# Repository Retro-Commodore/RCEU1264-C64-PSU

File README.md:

# C64-PSU
A C64/C128/Vic20/Plus4 PSU
This is a full replacement PSU with modern electronics that won't kill your computer when it gets bad.. the original PSU's short input to output, when they break, feeding approx 10v.
While it is possible to use wall warts, this design is created to be easy to diy, somewhat pretty and closer to the old designs with off the shelf items.

Greetz to Trap/Bonzai for being the source of inspiration to create this.

The PSU can be used for the C64 even with i.e. 1541 Ultimate and Vic20, and it's powerful enough to feed the C128 and/or 17xx REU.

All parts can be bought at [tme.eu](https://www.tme.eu/), and the pcb has been designed with parts from there.
A few parts like the DIN connector and fuse socket can be aqcuired from ebay where they're much cheaper.

*If you are a reseller, and use my designs, though the projects are open source, I'd like to ask you to donate a small amount of money, to cancer research for each sold device.*

The Mean Well IRM-20-5 is Short circuit / Overload / Over voltage protected (pdf's from Mean Well are in the documentation folder).

**The trafo is a 230v trafo, so countries that use 115v will need a different trafo.**

If you want to add an on/off switch, the easiest might be a switch on the 230v cable, or a round one, the round one is easiest to make holes to -by drilling-, rather than cutting a square one. But that is entirely up to you :-) .

The gerber files which is the zip file found in [hardware/eagle](https://github.com/Retro-Commodore/C64-PSU/tree/master/Hardware/Eagle Gerber) can be uploaded as is to PCB manufacturing companies like [JLCPCB](http://jlcpcb.com).

The PCB is created with Eagle which has a limiting size of 100x100mm (or is it 100x80mm?). And the PCB is within this size.
The newest version of KiCAD should be able to import the eagle files, in case you prefer this. 

**TODO**
* Add possibility to use PTC (one has to be sourced first), if you read this and know of one already please don't hesitate to add a ticket with the info. You'll providing the community a service :-)

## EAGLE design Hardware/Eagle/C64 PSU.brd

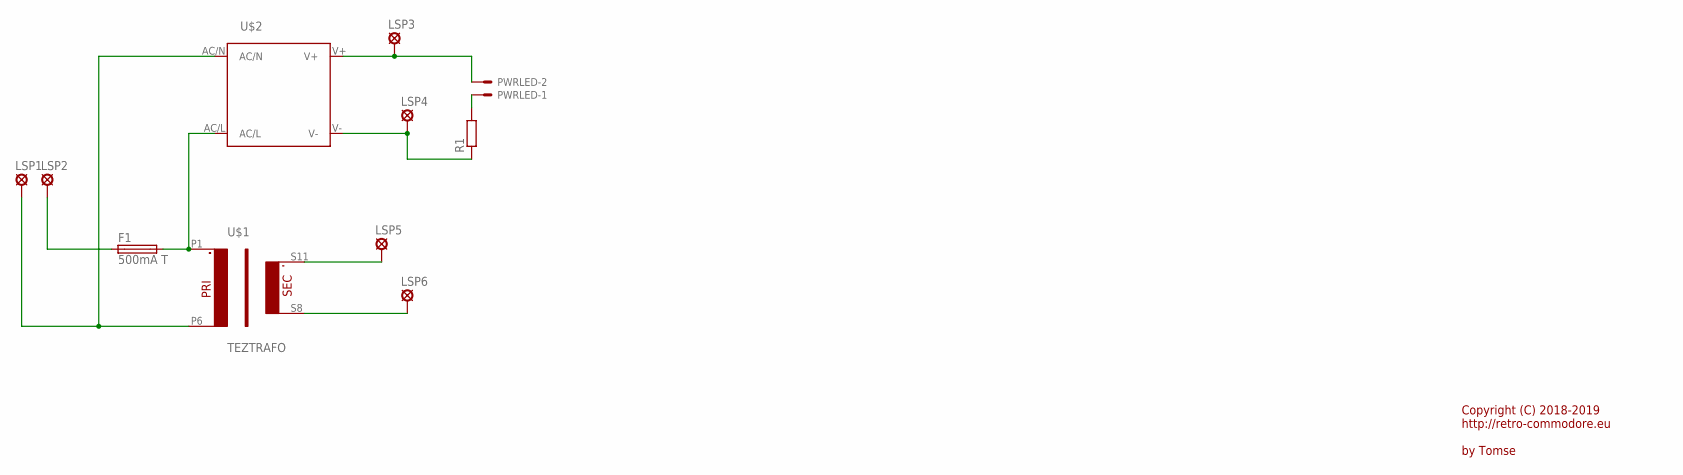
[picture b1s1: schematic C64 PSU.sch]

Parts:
F1: 500mA T; SH22,5
LSP1, LSP2, LSP3, LSP4, LSP5, LSP6: SE14
PWRLED: 22-23-2021
R1: R-EU_0207/10; 0207/10
U$1: TEZTRAFO; TEZ10/D230/9V
U$2: IRM_15/20IRM_15/20; IRM_15/20

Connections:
unnamed: F1.2, U$1.P1, U$2.AC/L
unnamed: LSP1.MP, U$1.P6, U$2.AC/N
unnamed: F1.1, LSP2.MP
unnamed: LSP6.MP, U$1.S8
unnamed: LSP5.MP, U$1.S11
unnamed: LSP4.MP, R1.1, U$2.V-
unnamed: LSP3.MP, PWRLED.2, U$2.V+
unnamed: PWRLED.1, R1.2

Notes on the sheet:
Copyright (C) 2018-2019 http://retro-commodore.eu by Tomse

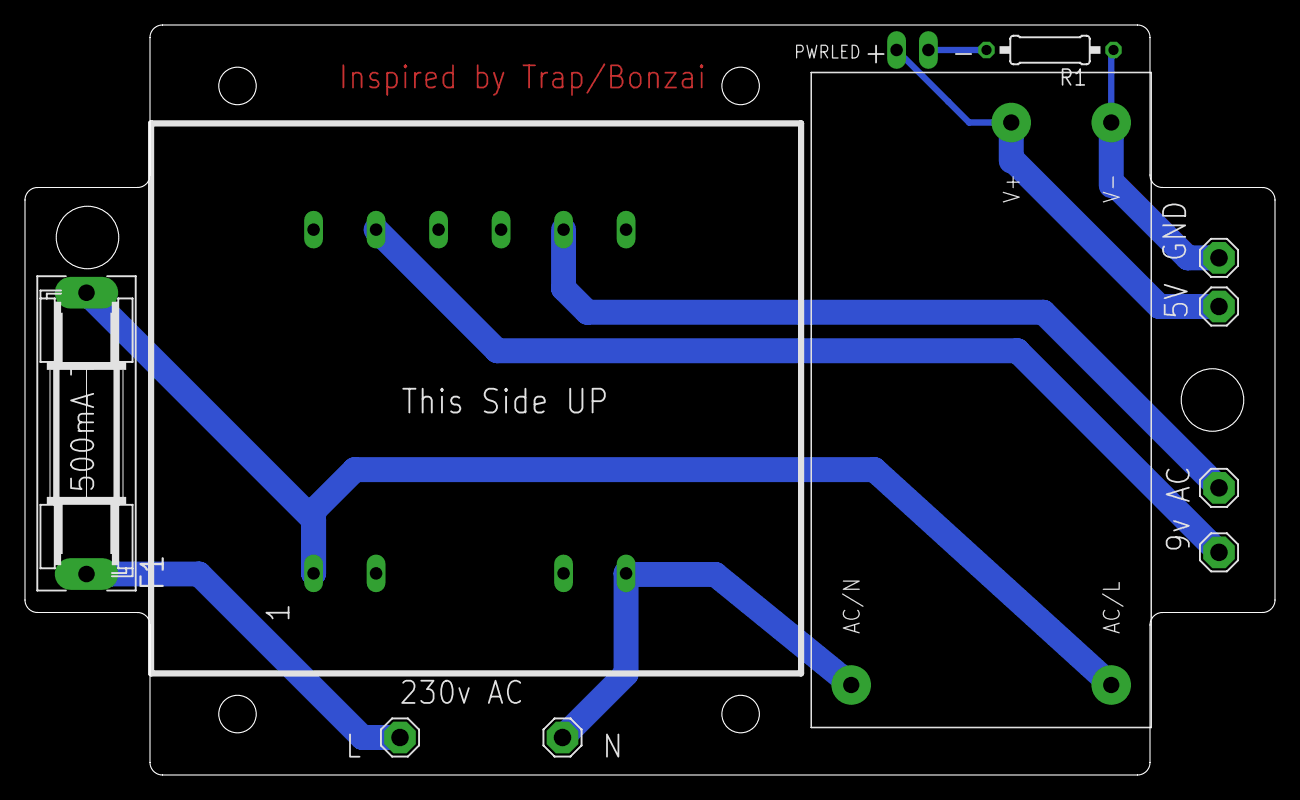
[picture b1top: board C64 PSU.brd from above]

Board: 2 copper layers, 100.0 x 60.0 mm, 11 parts (0 on the bottom side), 8 nets.

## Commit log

2019-01-15 Initial Relase
2019-01-15 Fixed solder pads for trafo
2019-01-16 Small updates based on ycombinator comments
2019-01-16 Added PDF documentation for the IRM-20-5
2019-01-16 Fixed correct trafo - added documentation for trafo
2019-06-26 added power led connectors
2019-06-28 Improved traces
2019-06-28 Updated Gerber with v1.4
2019-06-28 cosmetic changes
2019-06-28 Added documentation for LED
2019-07-19 Removed the 2A module
2019-10-14 Fixed text
2020-04-06 Fixing dirnaming
2021-09-18 Fixed correct fuse value
2023-09-07 Fixed url to enclosure and cleanup

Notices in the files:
Hardware/Eagle/C64 PSU.brd:
Copyright (c) 2018-2019 Retro Commodore
